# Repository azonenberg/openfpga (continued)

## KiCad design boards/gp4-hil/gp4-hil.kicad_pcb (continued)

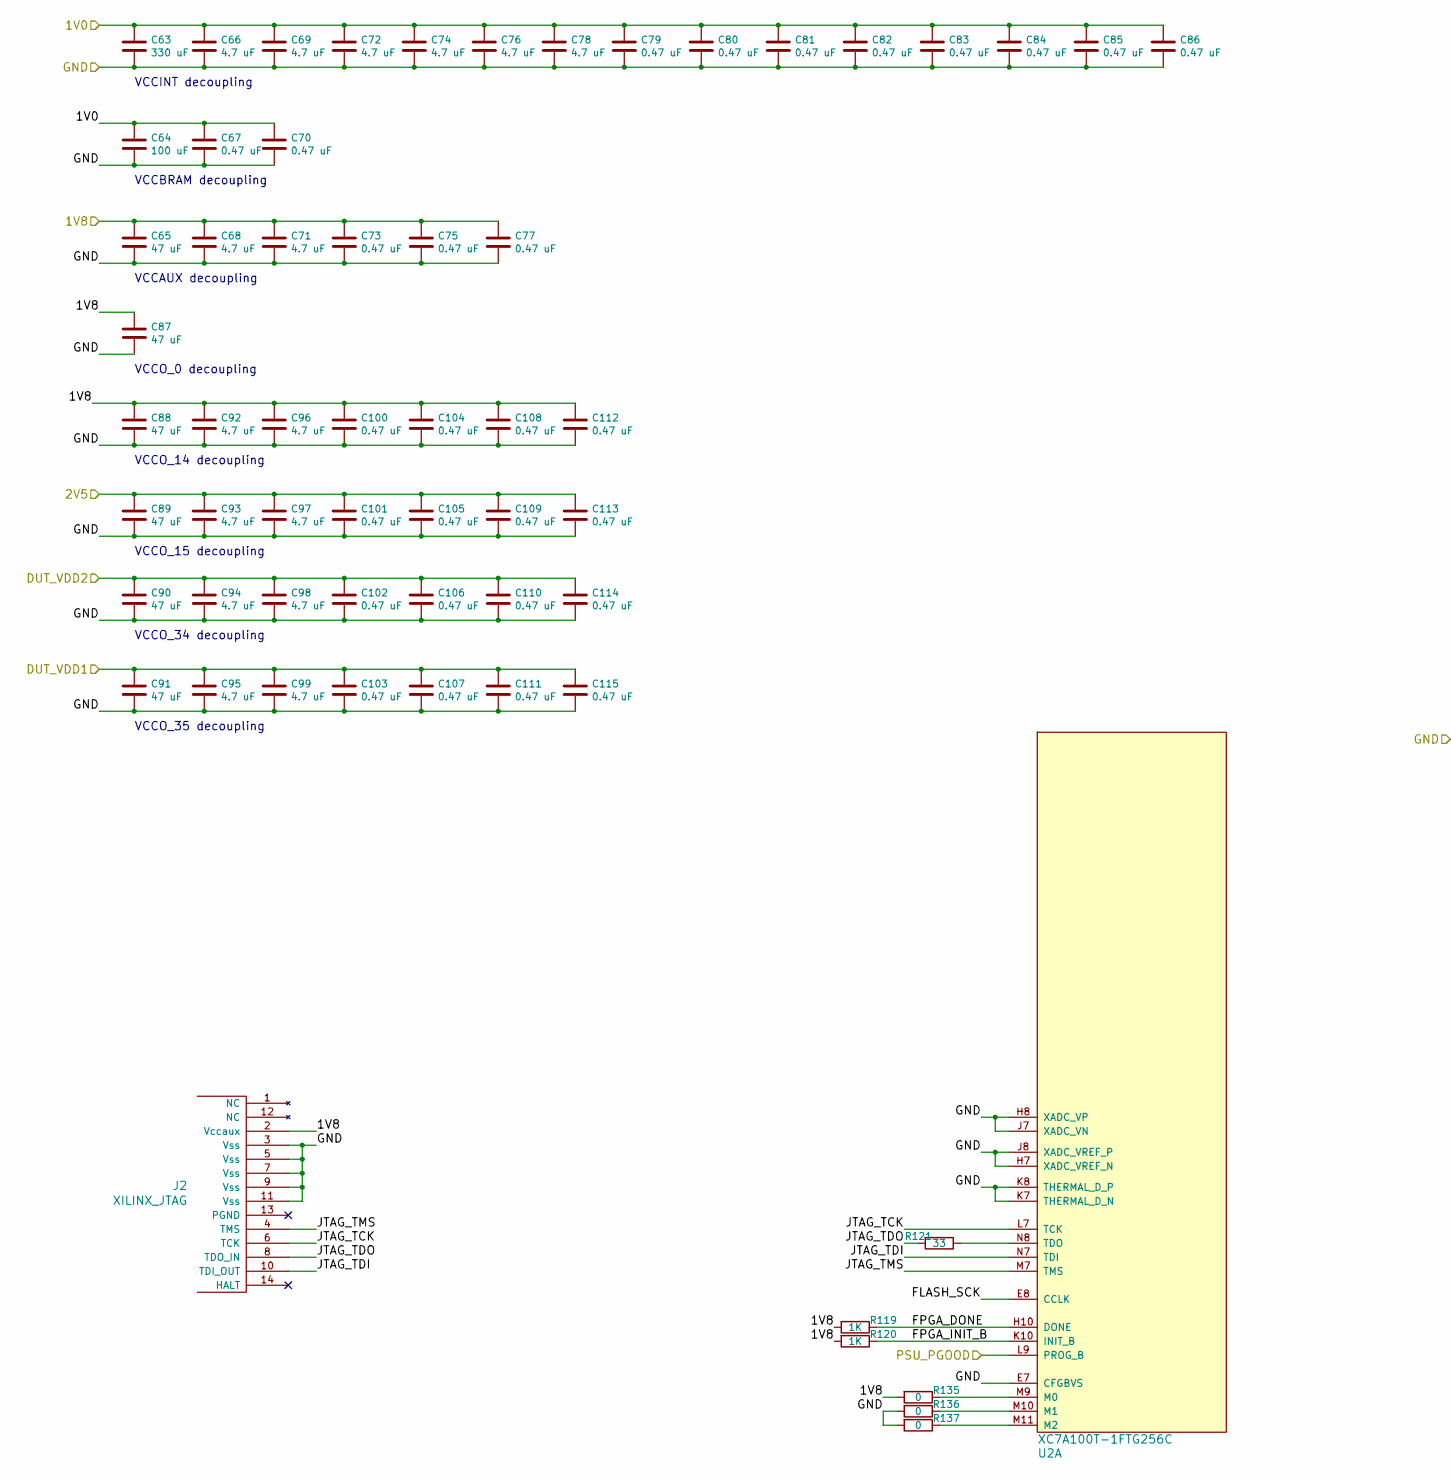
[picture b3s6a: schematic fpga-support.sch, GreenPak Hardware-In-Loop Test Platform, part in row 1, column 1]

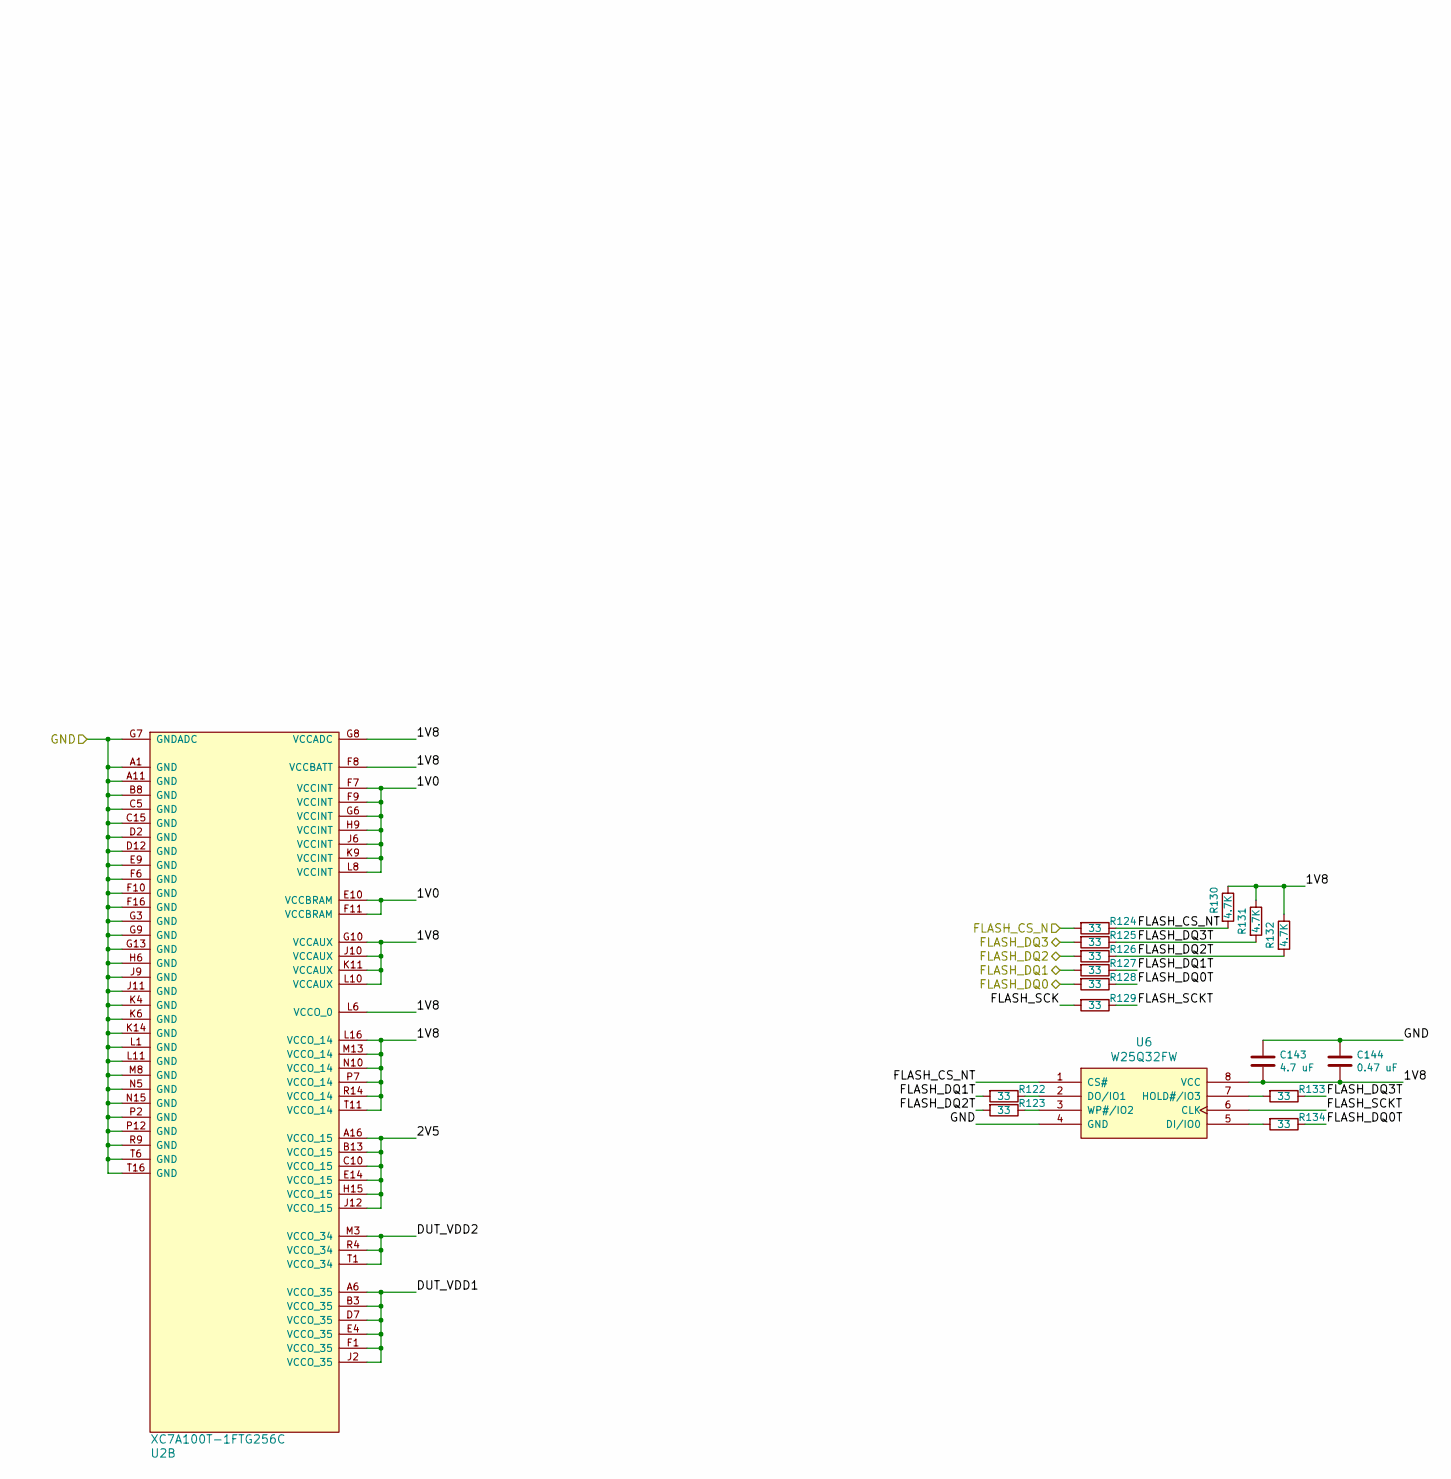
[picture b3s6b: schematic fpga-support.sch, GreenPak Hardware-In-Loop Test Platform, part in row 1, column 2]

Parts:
C63: 330 uF; EIA_1210_CAP_NOSILK
C64: 100 uF; EIA_1210_CAP_NOSILK
C65, C87, C88, C89, C90, C91: 47 uF; EIA_1206_CAP_NOSILK
C66, C68, C69, C71, C72, C74, C76, C78, C92, C93, C94, C95, C96, C97, C98, C99, C143: 4.7 uF; EIA_0603_CAP_NOSILK
C67, C70, C73, C75, C77, C79, C80, C81, C82, C83, C84, C85, C86, C100, C101, C102, C103, C104, C105, C106, C107, C108, C109, C110, C111, C112, C113, C114, C115, C144: 0.47 uF; EIA_0402_CAP_NOSILK
J2: XILINX_JTAG; XILINX_JTAG_PTH_MOLEX_0878311420
R119, R120: 1K; EIA_0402_RES_NOSILK
R121, R122, R123, R124, R125, R126, R127, R128, R129, R133, R134: 33; EIA_0402_RES_NOSILK
R130, R131, R132: 4.7K; EIA_0402_RES_NOSILK
R135, R136, R137: 0; EIA_0402_RES_NOSILK
U2: XC7A100T-1FTG256C; BGA_256_17x17_FULLARRAY_1MM
U6: W25Q32FW; DFN_8_1.27MM_6x5MM

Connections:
/Analog IO/1V8: C65.1, C68.1, C71.1, C73.1, C75.1, C77.1, C87.1, C88.1, C92.1, C96.1, C100.1, C104.1, C108.1, C112.1, C143.2, C144.2, J2.2 (Vccaux), R119.2, R120.2, R130.1, R131.1, R132.1, R135.2, U2.F8 (VCCBATT), U2.G8 (VCCADC), U2.G10 (VCCAUX), U2.J10 (VCCAUX), U2.K11 (VCCAUX), U2.L6 (VCCO_0), U2.L10 (VCCAUX), U2.L16 (VCCO_14), U2.M13 (VCCO_14), U2.N10 (VCCO_14), U2.P7 (VCCO_14), U2.R14 (VCCO_14), U2.T11 (VCCO_14), U6.8 (VCC); also elsewhere on the board
/Analog IO/2V5: C89.1, C93.1, C97.1, C101.1, C105.1, C109.1, C113.1, U2.A16 (VCCO_15), U2.B13 (VCCO_15), U2.C10 (VCCO_15), U2.E14 (VCCO_15), U2.H15 (VCCO_15), U2.J12 (VCCO_15); also elsewhere on the board
/Analog IO/DUT_VDD1: C91.1, C95.1, C99.1, C103.1, C107.1, C111.1, C115.1, U2.A6 (VCCO_35), U2.B3 (VCCO_35), U2.D7 (VCCO_35), U2.E4 (VCCO_35), U2.F1 (VCCO_35), U2.J2 (VCCO_35); also elsewhere on the board
/Analog IO/DUT_VDD2: C90.1, C94.1, C98.1, C102.1, C106.1, C110.1, C114.1, U2.M3 (VCCO_34), U2.R4 (VCCO_34), U2.T1 (VCCO_34); also elsewhere on the board
/Analog IO/GND: C63.2, C64.2, C65.2, C66.2, C67.2, C68.2, C69.2, C70.2, C71.2, C72.2, C73.2, C74.2, C75.2, C76.2, C77.2, C78.2, C79.2, C80.2, C81.2, C82.2, C83.2, C84.2, C85.2, C86.2, C87.2, C88.2, C89.2, C90.2, C91.2, C92.2, C93.2, C94.2, C95.2, C96.2, C97.2, C98.2, C99.2, C100.2, C101.2, C102.2, C103.2, C104.2, C105.2, C106.2, C107.2, C108.2, C109.2, C110.2, C111.2, C112.2, C113.2, C114.2, C115.2, C143.1, C144.1, J2.3 (Vss), J2.5 (Vss), J2.7 (Vss), J2.9 (Vss), J2.11 (Vss), R136.2, R137.2, U2.A1 (GND), U2.A11 (GND), U2.B8 (GND), U2.C5 (GND), U2.C15 (GND), U2.D2 (GND), U2.D12 (GND), U2.E7 (CFGBVS), U2.E9 (GND), U2.F6 (GND), U2.F10 (GND), U2.F16 (GND), U2.G3 (GND), U2.G7 (GNDADC), U2.G9 (GND), U2.G13 (GND), U2.H6 (GND), U2.H7 (XADC_VREF_N), U2.H8 (XADC_VP), U2.J7 (XADC_VN), U2.J8 (XADC_VREF_P), U2.J9 (GND), U2.J11 (GND), U2.K4 (GND), U2.K6 (GND), U2.K7 (THERMAL_D_N), U2.K8 (THERMAL_D_P), U2.K14 (GND), U2.L1 (GND), U2.L11 (GND), U2.M8 (GND), U2.N5 (GND), U2.N15 (GND), U2.P2 (GND), U2.P12 (GND), U2.R9 (GND), U2.T6 (GND), U2.T16 (GND), U6.4 (GND); also elsewhere on the board
/Ethernet + JTAG/FLASH_CS_N: R124.2; also elsewhere on the board
/Ethernet + JTAG/FLASH_DQ0: R128.2; also elsewhere on the board
/Ethernet + JTAG/FLASH_DQ1: R127.2; also elsewhere on the board
/Ethernet + JTAG/FLASH_DQ2: R126.2; also elsewhere on the board
/Ethernet + JTAG/FLASH_DQ3: R125.2; also elsewhere on the board
/FPGA support/1V0: C63.1, C64.1, C66.1, C67.1, C69.1, C70.1, C72.1, C74.1, C76.1, C78.1, C79.1, C80.1, C81.1, C82.1, C83.1, C84.1, C85.1, C86.1, U2.E10 (VCCBRAM), U2.F7 (VCCINT), U2.F9 (VCCINT), U2.F11 (VCCBRAM), U2.G6 (VCCINT), U2.H9 (VCCINT), U2.J6 (VCCINT), U2.K9 (VCCINT), U2.L8 (VCCINT); also elsewhere on the board
/FPGA support/FLASH_CS_NT: R124.1, R130.2, U6.1 (CS#)
/FPGA support/FLASH_DQ0T: R128.1, R134.1
/FPGA support/FLASH_DQ1T: R122.2, R127.1
/FPGA support/FLASH_DQ2T: R123.2, R126.1, R132.2
/FPGA support/FLASH_DQ3T: R125.1, R131.2, R133.1
/FPGA support/FLASH_SCK: R129.2, U2.E8 (CCLK)
/FPGA support/FLASH_SCKT: R129.1, U6.6 (CLK)
/FPGA support/FPGA_DONE: R119.1, U2.H10 (DONE)
/FPGA support/FPGA_INIT_B: R120.1, U2.K10 (INIT_B)
/FPGA support/JTAG_TCK: J2.6 (TCK), U2.L7 (TCK)
/FPGA support/JTAG_TDI: J2.10 (TDI_OUT), U2.N7 (TDI)
/FPGA support/JTAG_TDO: J2.8 (TDO_IN), R121.2
/FPGA support/JTAG_TMS: J2.4 (TMS), U2.M7 (TMS)
/FPGA support/PSU_PGOOD: U2.L9 (PROG_B); also elsewhere on the board
unnamed: R121.1, U2.N8 (TDO)
unnamed: R122.1, U6.2 (DO/IO1)
unnamed: R123.1, U6.3 (WP#/IO2)
unnamed: R133.2, U6.7 (HOLD#/IO3)
unnamed: R134.2, U6.5 (DI/IO0)
unnamed: R135.1, U2.M9 (M0)
unnamed: R136.1, U2.M10 (M1)
unnamed: R137.1, U2.M11 (M2)

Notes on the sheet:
VCCINT decoupling
VCCBRAM decoupling
VCCAUX decoupling
VCCO_0 decoupling
VCCO_14 decoupling
VCCO_15 decoupling
VCCO_34 decoupling
VCCO_35 decoupling

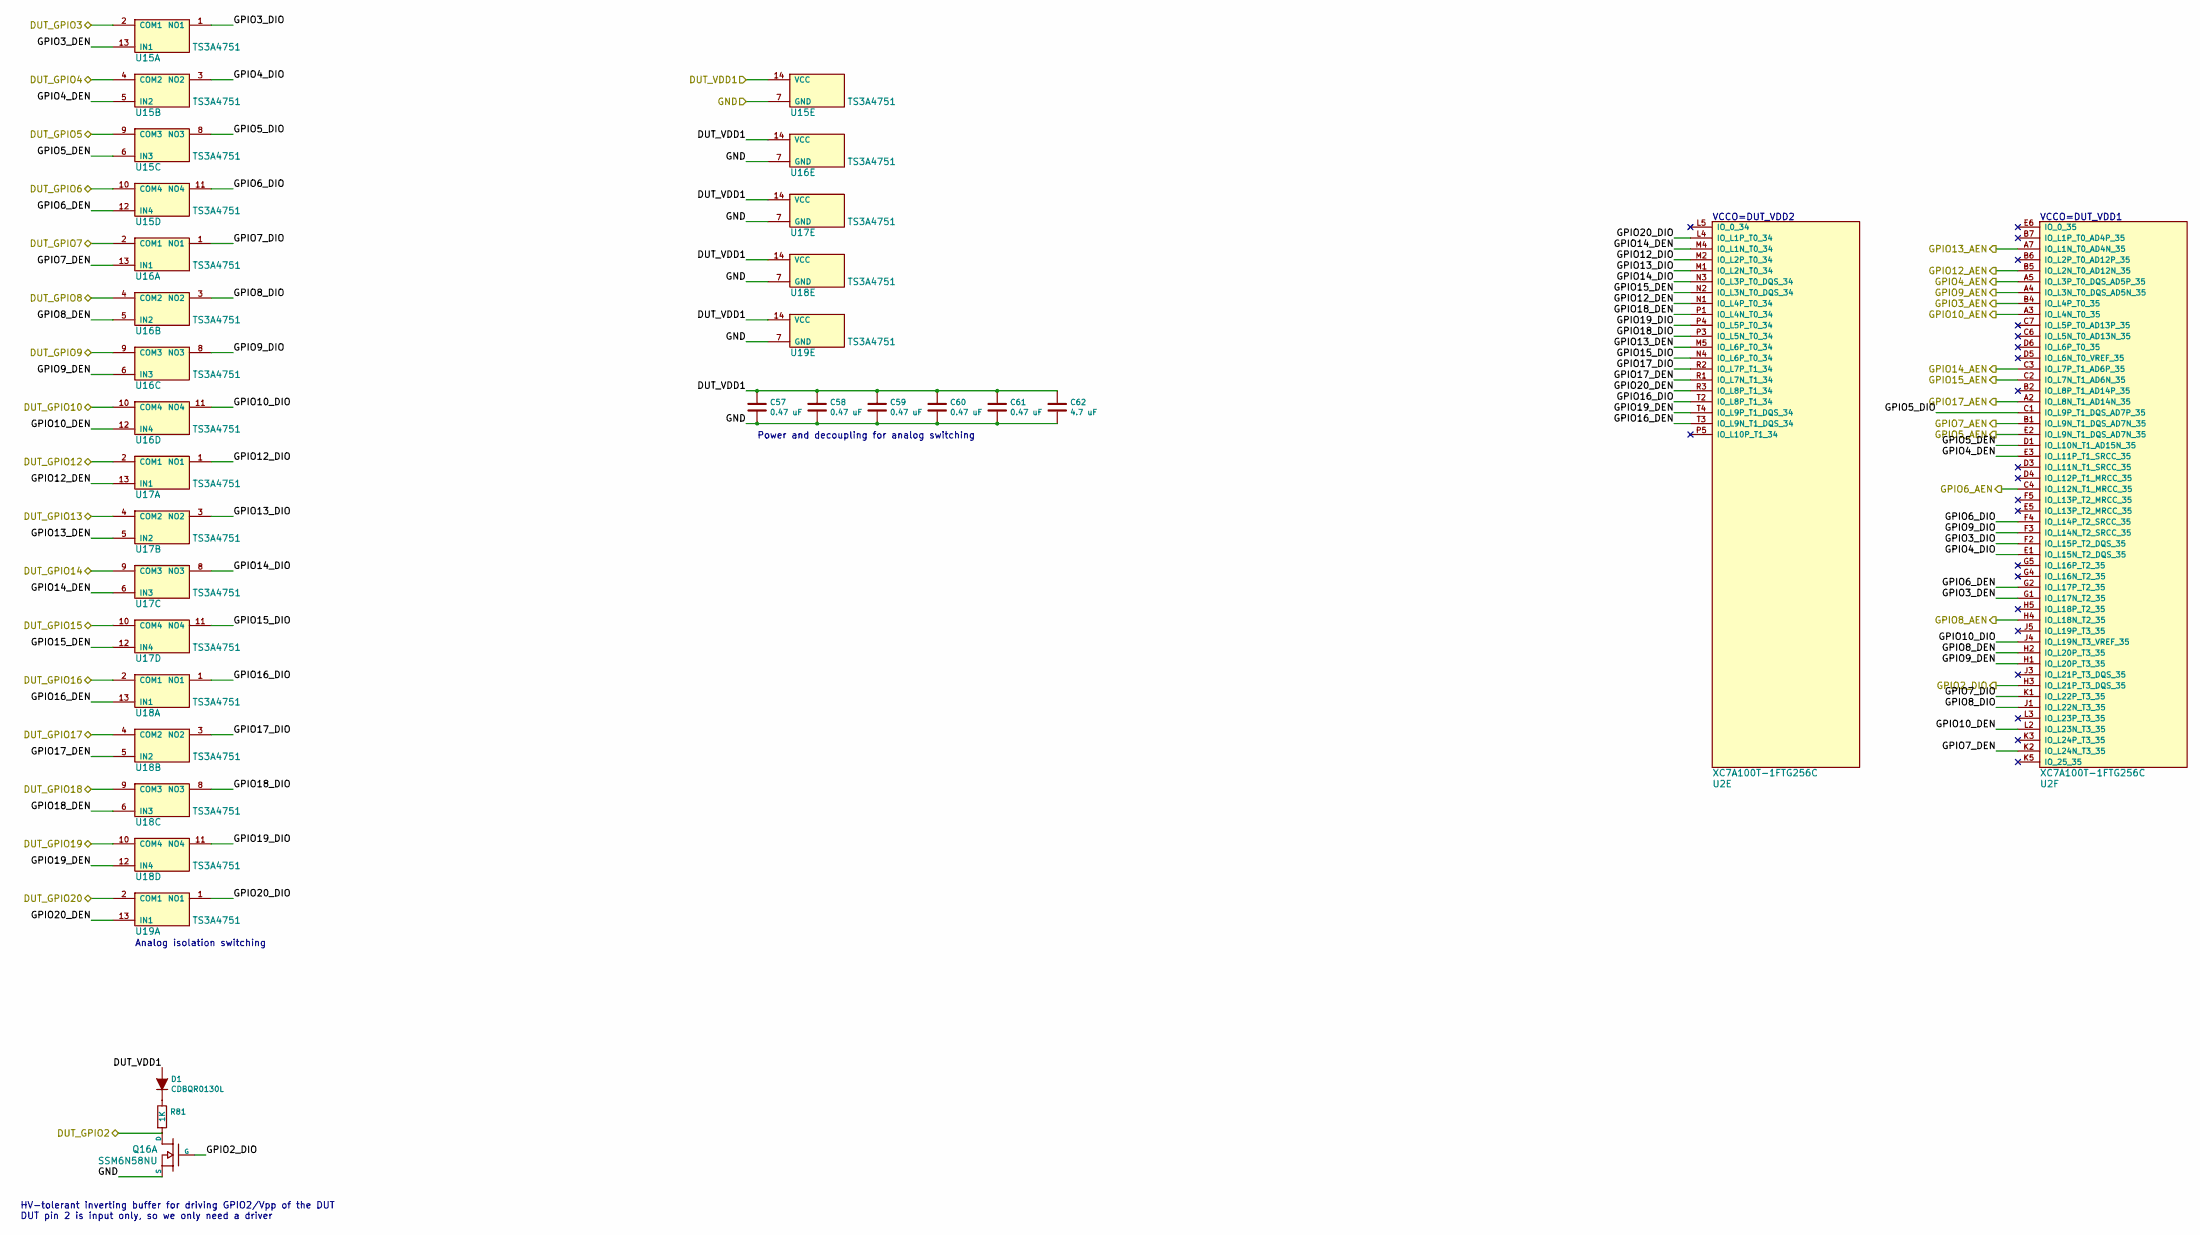
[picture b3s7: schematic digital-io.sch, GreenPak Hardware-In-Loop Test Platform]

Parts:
C57, C58, C59, C60, C61: 0.47 uF; EIA_0402_CAP_NOSILK
C62: 4.7 uF; EIA_0603_CAP_NOSILK
D1: CDBQR0130L; EIA_0402_LED
Q16: SSM6N58NU; DFN_6_0.65MM_2x2MM_GDS
R81: 1K; EIA_0402_RES_NOSILK
U2: XC7A100T-1FTG256C; BGA_256_17x17_FULLARRAY_1MM
U15, U16, U17, U18, U19: TS3A4751; QFN_14_0.4MM_2x2MM_TI_RUC

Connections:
/Analog IO/DUT_GPIO2: Q16.D1 (D), R81.2; also elsewhere on the board
/Analog IO/DUT_GPIO3: U15.2 (COM1); also elsewhere on the board
/Analog IO/DUT_GPIO4: U15.4 (COM2); also elsewhere on the board
/Analog IO/DUT_GPIO5: U15.9 (COM3); also elsewhere on the board
/Analog IO/DUT_GPIO6: U15.10 (COM4); also elsewhere on the board
/Analog IO/DUT_GPIO7: U16.2 (COM1); also elsewhere on the board
/Analog IO/DUT_GPIO8: U16.4 (COM2); also elsewhere on the board
/Analog IO/DUT_GPIO9: U16.9 (COM3); also elsewhere on the board
/Analog IO/DUT_GPIO10: U16.10 (COM4); also elsewhere on the board
/Analog IO/DUT_GPIO12: U17.2 (COM1); also elsewhere on the board
/Analog IO/DUT_GPIO13: U17.4 (COM2); also elsewhere on the board
/Analog IO/DUT_GPIO14: U17.9 (COM3); also elsewhere on the board
/Analog IO/DUT_GPIO15: U17.10 (COM4); also elsewhere on the board
/Analog IO/DUT_GPIO16: U18.2 (COM1); also elsewhere on the board
/Analog IO/DUT_GPIO17: U18.4 (COM2); also elsewhere on the board
/Analog IO/DUT_GPIO18: U18.9 (COM3); also elsewhere on the board
/Analog IO/DUT_GPIO19: U18.10 (COM4); also elsewhere on the board
/Analog IO/DUT_GPIO20: U19.2 (COM1); also elsewhere on the board
/Analog IO/DUT_VDD1: C57.1, C58.1, C59.1, C60.1, C61.1, C62.1, D1.2 (A), U15.14 (VCC), U16.14 (VCC), U17.14 (VCC), U18.14 (VCC), U19.14 (VCC); also elsewhere on the board
/Analog IO/GND: C57.2, C58.2, C59.2, C60.2, C61.2, C62.2, Q16.S1 (S), U15.7 (GND), U16.7 (GND), U17.7 (GND), U18.7 (GND), U19.7 (GND); also elsewhere on the board
/Analog IO/GPIO3_AEN: U2.B4 (IO_L4P_T0_35); also elsewhere on the board
/Analog IO/GPIO4_AEN: U2.A5 (IO_L3P_T0_DQS_AD5P_35); also elsewhere on the board
/Analog IO/GPIO5_AEN: U2.E2 (IO_L9N_T1_DQS_AD7N_35); also elsewhere on the board
/Analog IO/GPIO6_AEN: U2.C4 (IO_L12N_T1_MRCC_35); also elsewhere on the board
/Analog IO/GPIO7_AEN: U2.B1 (IO_L9N_T1_DQS_AD7N_35); also elsewhere on the board
/Analog IO/GPIO8_AEN: U2.H4 (IO_L18N_T2_35); also elsewhere on the board
/Analog IO/GPIO9_AEN: U2.A4 (IO_L3N_T0_DQS_AD5N_35); also elsewhere on the board
/Analog IO/GPIO10_AEN: U2.A3 (IO_L4N_T0_35); also elsewhere on the board
/Analog IO/GPIO12_AEN: U2.B5 (IO_L2N_T0_AD12N_35); also elsewhere on the board
/Analog IO/GPIO13_AEN: U2.A7 (IO_L1N_T0_AD4N_35); also elsewhere on the board
/Analog IO/GPIO14_AEN: U2.C3 (IO_L7P_T1_AD6P_35); also elsewhere on the board
/Analog IO/GPIO15_AEN: U2.C2 (IO_L7N_T1_AD6N_35); also elsewhere on the board
/Analog IO/GPIO17_AEN: U2.A2 (IO_L8N_T1_AD14N_35); also elsewhere on the board
/DUT/GPIO2_DIO: Q16.G1 (G), U2.H3 (IO_L21P_T3_DQS_35); also elsewhere on the board
/Digital IO/GPIO3_DEN: U2.G1 (IO_L17N_T2_35), U15.13 (IN1)
/Digital IO/GPIO3_DIO: U2.F2 (IO_L15P_T2_DQS_35), U15.1 (NO1)
/Digital IO/GPIO4_DEN: U2.E3 (IO_L11P_T1_SRCC_35), U15.5 (IN2)
/Digital IO/GPIO4_DIO: U2.E1 (IO_L15N_T2_DQS_35), U15.3 (NO2)
/Digital IO/GPIO5_DEN: U2.D1 (IO_L10N_T1_AD15N_35), U15.6 (IN3)
/Digital IO/GPIO5_DIO: U2.C1 (IO_L9P_T1_DQS_AD7P_35), U15.8 (NO3)
/Digital IO/GPIO6_DEN: U2.G2 (IO_L17P_T2_35), U15.12 (IN4)
/Digital IO/GPIO6_DIO: U2.F4 (IO_L14P_T2_SRCC_35), U15.11 (NO4)
/Digital IO/GPIO7_DEN: U2.K2 (IO_L24N_T3_35), U16.13 (IN1)
/Digital IO/GPIO7_DIO: U2.K1 (IO_L22P_T3_35), U16.1 (NO1)
/Digital IO/GPIO8_DEN: U2.H2 (IO_L20P_T3_35), U16.5 (IN2)
/Digital IO/GPIO8_DIO: U2.J1 (IO_L22N_T3_35), U16.3 (NO2)
/Digital IO/GPIO9_DEN: U2.H1 (IO_L20P_T3_35), U16.6 (IN3)
/Digital IO/GPIO9_DIO: U2.F3 (IO_L14N_T2_SRCC_35), U16.8 (NO3)
/Digital IO/GPIO10_DEN: U2.L2 (IO_L23N_T3_35), U16.12 (IN4)
/Digital IO/GPIO10_DIO: U2.J4 (IO_L19N_T3_VREF_35), U16.11 (NO4)
/Digital IO/GPIO12_DEN: U2.N1 (IO_L4P_T0_34), U17.13 (IN1)
/Digital IO/GPIO12_DIO: U2.M2 (IO_L2P_T0_34), U17.1 (NO1)
/Digital IO/GPIO13_DEN: U2.M5 (IO_L6P_T0_34), U17.5 (IN2)
/Digital IO/GPIO13_DIO: U2.M1 (IO_L2N_T0_34), U17.3 (NO2)
/Digital IO/GPIO14_DEN: U2.M4 (IO_L1N_T0_34), U17.6 (IN3)
/Digital IO/GPIO14_DIO: U2.N3 (IO_L3P_T0_DQS_34), U17.8 (NO3)
/Digital IO/GPIO15_DEN: U2.N2 (IO_L3N_T0_DQS_34), U17.12 (IN4)
/Digital IO/GPIO15_DIO: U2.N4 (IO_L6P_T0_34), U17.11 (NO4)
/Digital IO/GPIO16_DEN: U2.T3 (IO_L9N_T1_DQS_34), U18.13 (IN1)
/Digital IO/GPIO16_DIO: U2.T2 (IO_L8P_T1_34), U18.1 (NO1)
/Digital IO/GPIO17_DEN: U2.R1 (IO_L7N_T1_34), U18.5 (IN2)
/Digital IO/GPIO17_DIO: U2.R2 (IO_L7P_T1_34), U18.3 (NO2)
/Digital IO/GPIO18_DEN: U2.P1 (IO_L4N_T0_34), U18.6 (IN3)
/Digital IO/GPIO18_DIO: U2.P3 (IO_L5N_T0_34), U18.8 (NO3)
/Digital IO/GPIO19_DEN: U2.T4 (IO_L9P_T1_DQS_34), U18.12 (IN4)
/Digital IO/GPIO19_DIO: U2.P4 (IO_L5P_T0_34), U18.11 (NO4)
/Digital IO/GPIO20_DEN: U2.R3 (IO_L8P_T1_34), U19.13 (IN1)
/Digital IO/GPIO20_DIO: U2.L4 (IO_L1P_T0_34), U19.1 (NO1)
unnamed: D1.1 (K), R81.1

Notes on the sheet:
Analog isolation switching
VCCO=DUT_VDD2
VCCO=DUT_VDD1
HV-tolerant inverting buffer for driving GPIO2/Vpp of the DUT DUT pin 2 is input only, so we only need a driver
Power and decoupling for analog switching

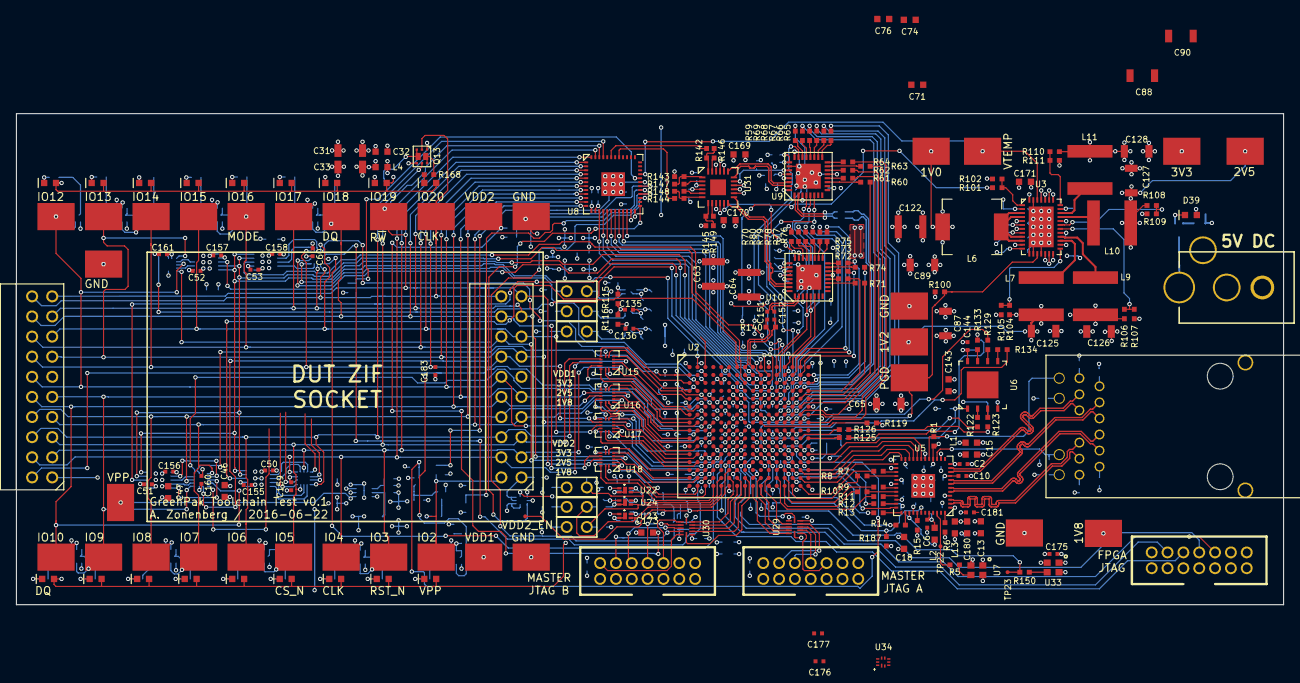
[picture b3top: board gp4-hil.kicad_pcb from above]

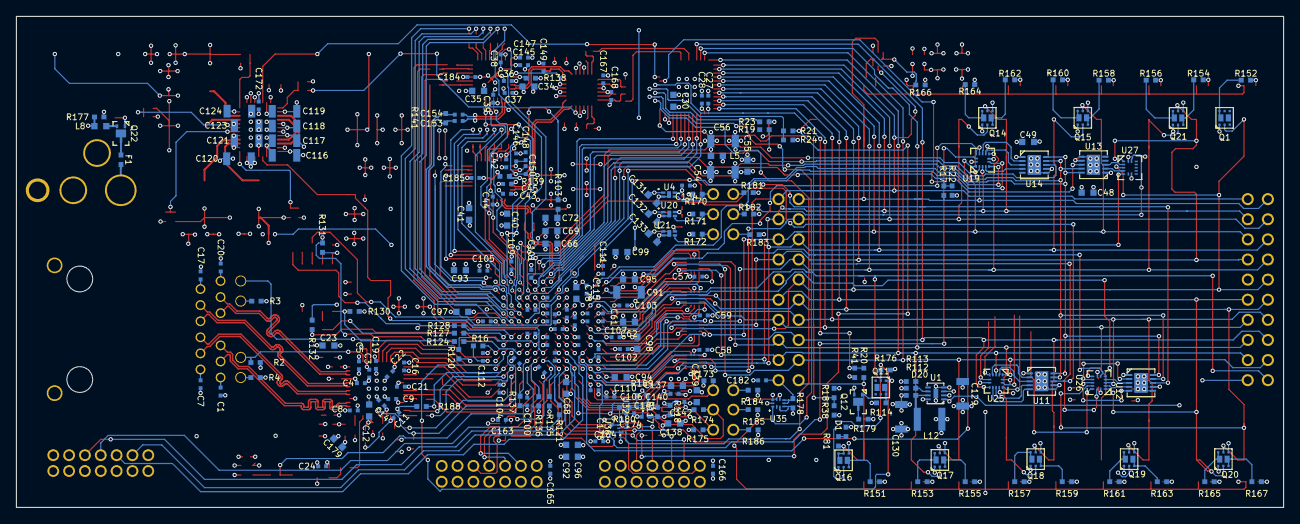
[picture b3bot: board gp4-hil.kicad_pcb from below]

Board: 4 copper layers, 160.0 x 62.0 mm, 450 parts (231 on the bottom side), 365 nets.

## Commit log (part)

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2017-07-06 Minor indentation fix
2017-07-07 Finished initial JtagPipeBridge implementation
2017-07-07 Fixed several bugs in XC2C emulator. Now runs a more complex blinky bitstream correctly.
2017-07-08 Fixed typo
2017-07-12 Updated gp4-stqfn-thermal with correct pinout for 20-pin header (PCB rev 0.2)
2017-07-13 Continued initial netlist reading support
2017-07-13 Added bitstream reading support for abuf, flipflop, pwrdet, POR
2017-07-13 PGA: added bitstream loading support
2017-07-21 Now loading LF/ring oscillator bitstreams
2017-07-21 Removed possible uninitilaized speed if process is typo'd
2017-07-21 Added attribute to tell ubsan that the RNG's integer overflow is intentional
2017-07-21 Added bitstream loading support for DELAY and SHREG
2017-08-07 Implemented bitstream loading for IOB type A, ACMP, VREF
2017-08-07 ReadMatrixSelector - demoted spammy message from debug to trace verbosity
2017-08-07 Finished initial bitstream loading support for counters
2017-08-07 Added gpkjson cell dump database
2017-08-07 Added initial netlist export. Probably not fully functional for connectivity; definitely does not support attributes yet.
2017-08-08 Initial commit of Yosys netlist crate
2017-08-08 yosys-netlist-json: Get the special 01xz-or-number working
2017-08-08 yosys-netlist-json: Add Default; Move main read function into an impl
2017-08-08 xc2bit: Add information about the location of the global signals
2017-08-08 xc2bit: Add registers to structure.rs
2017-08-08 xc2bit: Add ZIA to structure.rs
2017-08-08 xc2bit-jed2json: Very initial beginnings of converting jed to json
2017-08-08 xc2bit-jed2json: Output all cell types to json
    Not all attributes are output correctly yet
2017-08-08 xc2bit-jed2json: Write attributes of IOBs to json
2017-08-08 xc2bit-jed2json: Make OR terms connect to nets properly
2017-08-08 xc2bit-jed2json: fix bugs in XOR and connect REG to nets
2017-08-08 xc2bit-jed2json: Final fixups to make json proper
2017-08-08 xc2bit-jed2json: Misc. ZIA-related bugfixes for jed2json
2017-08-08 xc2bit-jed2json: Fix up duplicated code for constructing cells
2017-08-08 xc2bit-jed2json: More refactoring of wire-adding code
2017-08-08 xc2bit-jed2json: Wrap some over-long lines
2017-08-09 Implemented attribute/parameter handling on Greenpak4PairedEntity
2017-08-11 Added Counter test
2017-08-15 gpkjson now aborts correctly when loading the input fails
2017-08-15 Fixed bug in PGEN bitstream loading
2017-08-28 Greenpak4Delay: Fixed missing quotes in GP_EDGEDET JSON export
2017-09-04 Added a fabric counter to the Counter test
2017-09-18 yosys-netlist-json: Derive Hash where useful
2017-09-18 xbpar-rs: Fix BasePAREngine unsafety
    Still some weirdness going on with lifetimes
2017-09-18 xbpar-rs: Fix mating unsafety??? and add associated data
2017-09-18 xbpar-rs: Can complete much more stuff
2017-09-18 xbpar_ffi: Expose all of the PAREngine base methods
2017-09-18 xbpar-rs: Wrap edges, nodes, and graphs
2017-09-18 xbpar_ffi: Fix typos
2017-09-18 xc2par: XXX was xc2bit: Expose ZIA map
2017-09-18 xbpar-rs: Wrap the easy parts of PAREngine
2017-09-18 xbpar-rs: Remove get_node_by_index_mut_pair unsafety
2017-09-18 xbpar_ffi: Start exposing bits of the PAREngine
2017-09-18 xc2par: Initial commit
2017-09-18 xbpar-rs: Enough to not instantly crash
2017-09-18 xc2par: Create all non-ZIA-related nodes/edges
2017-09-18 xbpar-rs: have d/n instead of 0/1
2017-09-18 xbpar-rs: Demo works
2017-09-18 xc2par: Make ZIA connections (untested)
2017-09-18 xc2par: Convert input to a graph in a hacky way
2017-09-18 xc2par: Add some more Debug traits
2017-09-18 xc2par: Load yosys netlist files
2017-09-18 xbpar_ffi: Add override
2017-09-18 xc2par: Debug back to old flaky state
2017-09-18 xc2par: Completely untested replacement of yosys json parsing
2017-09-18 xc2par: Probably-not-working rewrite to use structure.rs
2017-09-18 xc2par: Working on fighting the borrow checker
2017-09-18 xc2par: Misc tweaking in netlist.rs
2017-09-18 xc2par: Fix all nondeterminism
2017-09-18 xc2par: Work on fixing new structure.rs
2017-09-18 xc2par: Add nodes representing ZIA outputs to FBs
    This is needed to figure out which row is supposed to be used
2017-09-18 xc2par: Add some missing fields
2017-09-18 xc2par: Simple and gate test now works all the time
2017-09-18 xc2par: Load all valid cell types
2017-09-18 xc2par: Implement very initial register support
2017-09-18 xc2par: Implement feedback in output.rs
    Poorly-tested because yosys needs work. Also, some structures don't get
    past the PAR stage for some reason.
2017-10-22 hidapi-linux: Mark `dev` unused for now
2017-11-03 xc2par: Hook up xc2par to CMake
2017-11-03 xc2par: Add whatever squashed fragments remain from abandoned attempts
    Previously here was an attempt to use xbpar. This is being replaced with
    a custom Coolrunner-II-specific PAR engine. This is a giant squash
    commit of all old code.
2017-11-03 xc2par: Implement FBn_Pi locations for placing product terms
2017-11-03 xc2par: Incomplete work for assigning p-terms
2017-11-03 xc2par: More work on assigning p-terms
2017-11-03 xc2par: Implement ZIA routing algorithm
2017-11-03 xc2par: Implement untested min-conflicts algorithm
2017-11-03 xc2par: Giant hack to successfully output AND terms
2017-11-14 build: Add an option to disable building hardware-interfacing code
2017-11-14 contrib: Add a demo of using emscripten-compiled gp4par
2017-11-18 xc2par: Rename NetlistLocation to RequestedLocation
2017-11-18 xc2par: Derive useful traits on new data structures
2017-11-18 xc2par: Convert InBuf to new data structure
2017-11-18 xc2par: Convert product terms to the new format
    Also no longer creates ZIA dummy buffers. Yes, this breaks other code.
2017-11-18 xc2par: Mark which macrocell feedback options are used
2017-11-18 xc2par: Finish converting registers to new format
    Does not quite work due to handling of vss/vdd
2017-11-18 xc2par: Finish building new data structures
2017-11-18 xc2par: Improve objpool iterators; Work on force-duplicating pterms
2017-11-18 xc2par: Replace objectpool iterators with Vec's iterators
2017-11-19 xc2par: Untested rewrite of ZIA assigning to use new data structures
2017-11-19 xc2par: First pass of cleaning up engine
    Note that output still doesn't work
2017-11-19 xc2par: Implement updating "reverse" pointers
2017-11-19 xc2par: Write out OR/XOR bits properly
2017-11-19 xc2par: Implement outputting most of the remaining bits
2017-11-19 xc2par: Clean up some ugly types in engine.rs
2017-11-28 xc2bit: Remove manual Clone traits
    This is no longer necessary as of Rust 1.21
2017-12-05 xc2par: Fix retrieving LOC from netlist
2017-12-19 xc2par: Implement proper location handling of global nets
2017-12-21 xc2par: Refactor: p-term assignment doesn't need to leak out
    This information is already available redundantly
2017-12-21 xc2par: Some more minor cleanups
2017-12-21 xc2par: Make ZIA assigning only require macrocell placements
    It now no longer requires product-term placements. This is possible
    because every ZIA choice is available to be used in every product term.
    This is useful because it allows both types of "badness" scores to be
    calculated and combined together.
2017-12-22 xc2par: Make incorrectly-paired macrocells actually contribute to score
2017-12-22 xc2par: New p-term placer
2017-12-22 xc2bit: Make everything serde-serializable
    This isn't used in the library, but it can be useful for consumers of
    the library to be able to dump bitstream data for debugging
2017-12-22 xc2par: Remove port names in intermediate graph
    These are no longer used
2017-12-22 xc2bit: Remove XC2ZIARowPiece
    It is redundant and simply wraps an XC2ZIAInput
2018-01-17 jedec: Copy out into separate crate
2018-01-18 jedec: "Support" (ignore) more field types
2018-01-18 xc2bit: Move reftests into the top-level tests/ directory
    Finally fixes #105
2018-01-18 xc2bit: Begin refactor to use new saner jed writing
2018-01-18 xc2bit: Finish refactor to use new jed writing system
2018-01-18 jedec: Add a write function that has periodic linebreaks
2018-01-18 xc2par: Begin writing tests for the frontend.rs logic
2018-01-19 xc2par: Parse some more IO-related attributes
    Round-tripping a very basic design now works.
2018-01-19 xc2par: Add some initial reftests for netlist.rs
    These are just copies of the frontend reftests. More tests need to be
    written for various rules and error conditions.
2018-03-22 xc2par: Add some very basic PAR reftests
2018-03-22 xc2par: Work on chasing down some bugs in the min-conflicts logic
2018-03-23 xc2par: "Fix" issue with state mutation when PAR is done
    TODO: Investigate why this is necessary. This seems like it should not
    be happening.
2018-03-23 xc2par: Fix a new source of nondeterminism
2018-03-23 xc2par: Move the first piece into OutputGraph
2018-03-23 xc2par: Move all output fields to new data structure
2018-03-23 xc2par: Clean up try_assign_fb
    It now outputs the "scoring" outputs to a dummy output. It also makes
    its own copy of the input assignments rather than carefully mutating and
    un-mutating. These together try and prevent bugs.
2018-04-05 xc2bit: Refactor global bits into a new file
2018-04-05 xc2bit: Bit twiddling can handle defaults and Result
2018-04-05 bittwidder: Refactor out attribute parsing
2018-04-09 xc2bit: First port to using new bittwiddler
2018-04-09 bittwiddler: Fix struct
2018-04-09 xc2bit: Use bittwiddler for macrocell jed mode
2018-04-09 xc2bit: Take Write by value
2018-04-22 xc2bit: Begin attempting to convert IOBs to use small arrays
2018-05-04 xc2par: Hook up slog logging in frontend
2018-05-04 xc2par: Add error handling for macrocell gather function
    Also downgrade a lot of messages to debug level
2018-05-09 xc2par: Add incomplete logging to PAR engine
2018-05-12 xc2par: Misc logging and cleanup
2018-05-12 xc2par: Plumb in most of the support for non-32A devices
2018-05-13 xc2par: Rust 1.26 finally stabilized slice patterns. Hallelujah!
2018-05-13 xc2par: Much nicer frontend - actually usable?
2018-05-13 xc2bit: Add versions to satisfy crates.io
2018-05-13 xc2par: Update crates.io metadata
2018-06-01 xc2par: Fix bug where sometimes input graph generation would panic
    The algorithm assumes that all "macrocell-related" intermediate graph
    objects are already in the map. This assumption was violated because of
    forgetting to add every macrocell bit coming out of the gather function
    (only the bit directly returned by the gather function was added).
2018-06-01 xc2par: Fix actually using the direct-path register
2018-09-12 Update logtools to bring in Windows ERROR fix.
2020-02-09 xc2par: Update Error cause->source
2020-02-09 xc2par: Handle new way that yosys can encode attributes
    Yosys commits 15fae357f6c7a5c205d2733cd0b2640eecd17a2d and
    00fba627118fb536686b3d30f3b81f71b513cd51 changed how numeric parameters
    are encoded into JSON output. The new format will store them as a base-2
    string rather than a raw number.
2020-02-10 xc2par: More debug messages and pretty json output
2020-03-01 xc2par: Add forgotten tests for constant output
2020-03-08 Dummy 64a ZIA entries so crbit conversion will work
2020-03-15 jedec: Remove deprecated error description
2020-03-15 xc2bit: Remove deprecated error description
2020-03-15 rust: Enable 2018 edition
2020-03-15 bittwiddler: Update dependencies
2020-03-22 xc2bit: Make iob.rs use Display
